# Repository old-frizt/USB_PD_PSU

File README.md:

# USB_PD_PSU
DIY USB Power Delivery Lab Bench Power Supply

WORK-IN-PROGRESS

This is a power supply with a linear ouput stage and a switching pre regulator.
In the future it will be controlled via a microcontroller doughter board.

The power to the supply is comes from USB Power-delivery at 20V.
The ouput can be set between 0-20V and 0-3A.

Additional information can be found on my website: https://arduonics.com/2020/electronics/diy-usb-power-delivery-lab-bench-power-supply/

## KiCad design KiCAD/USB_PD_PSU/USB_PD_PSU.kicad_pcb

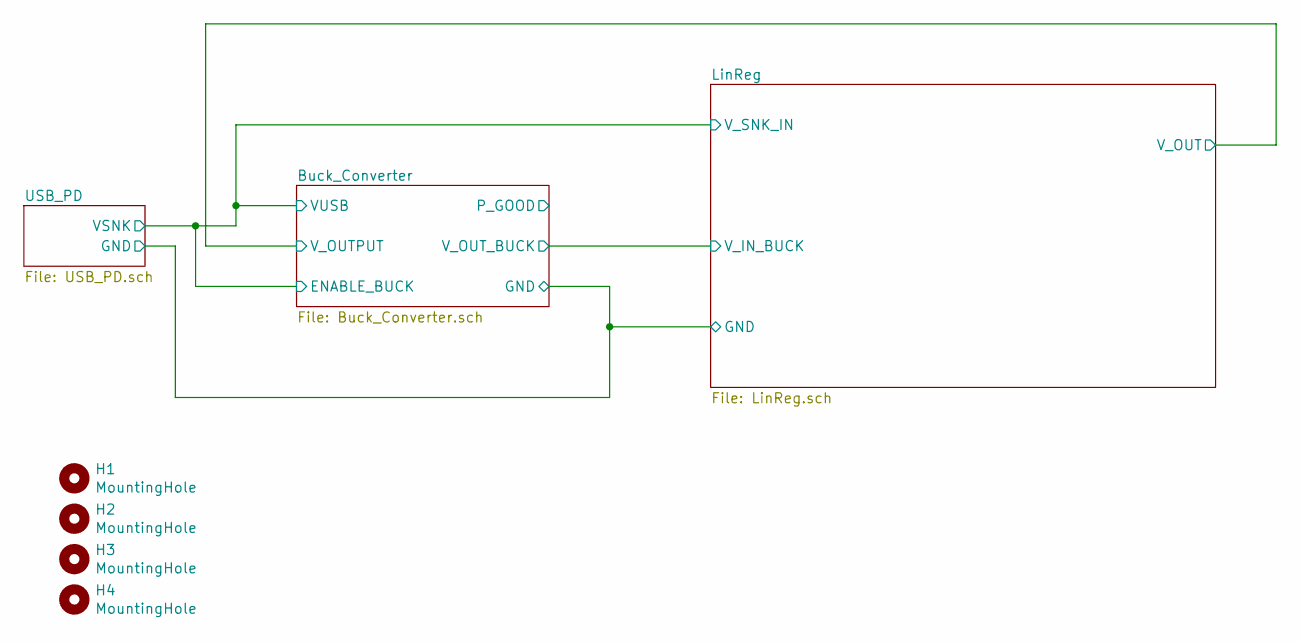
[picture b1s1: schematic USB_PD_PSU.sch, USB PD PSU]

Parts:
H1, H2, H3, H4: MountingHole; MountingHole_3.2mm_M3_Pad_Via

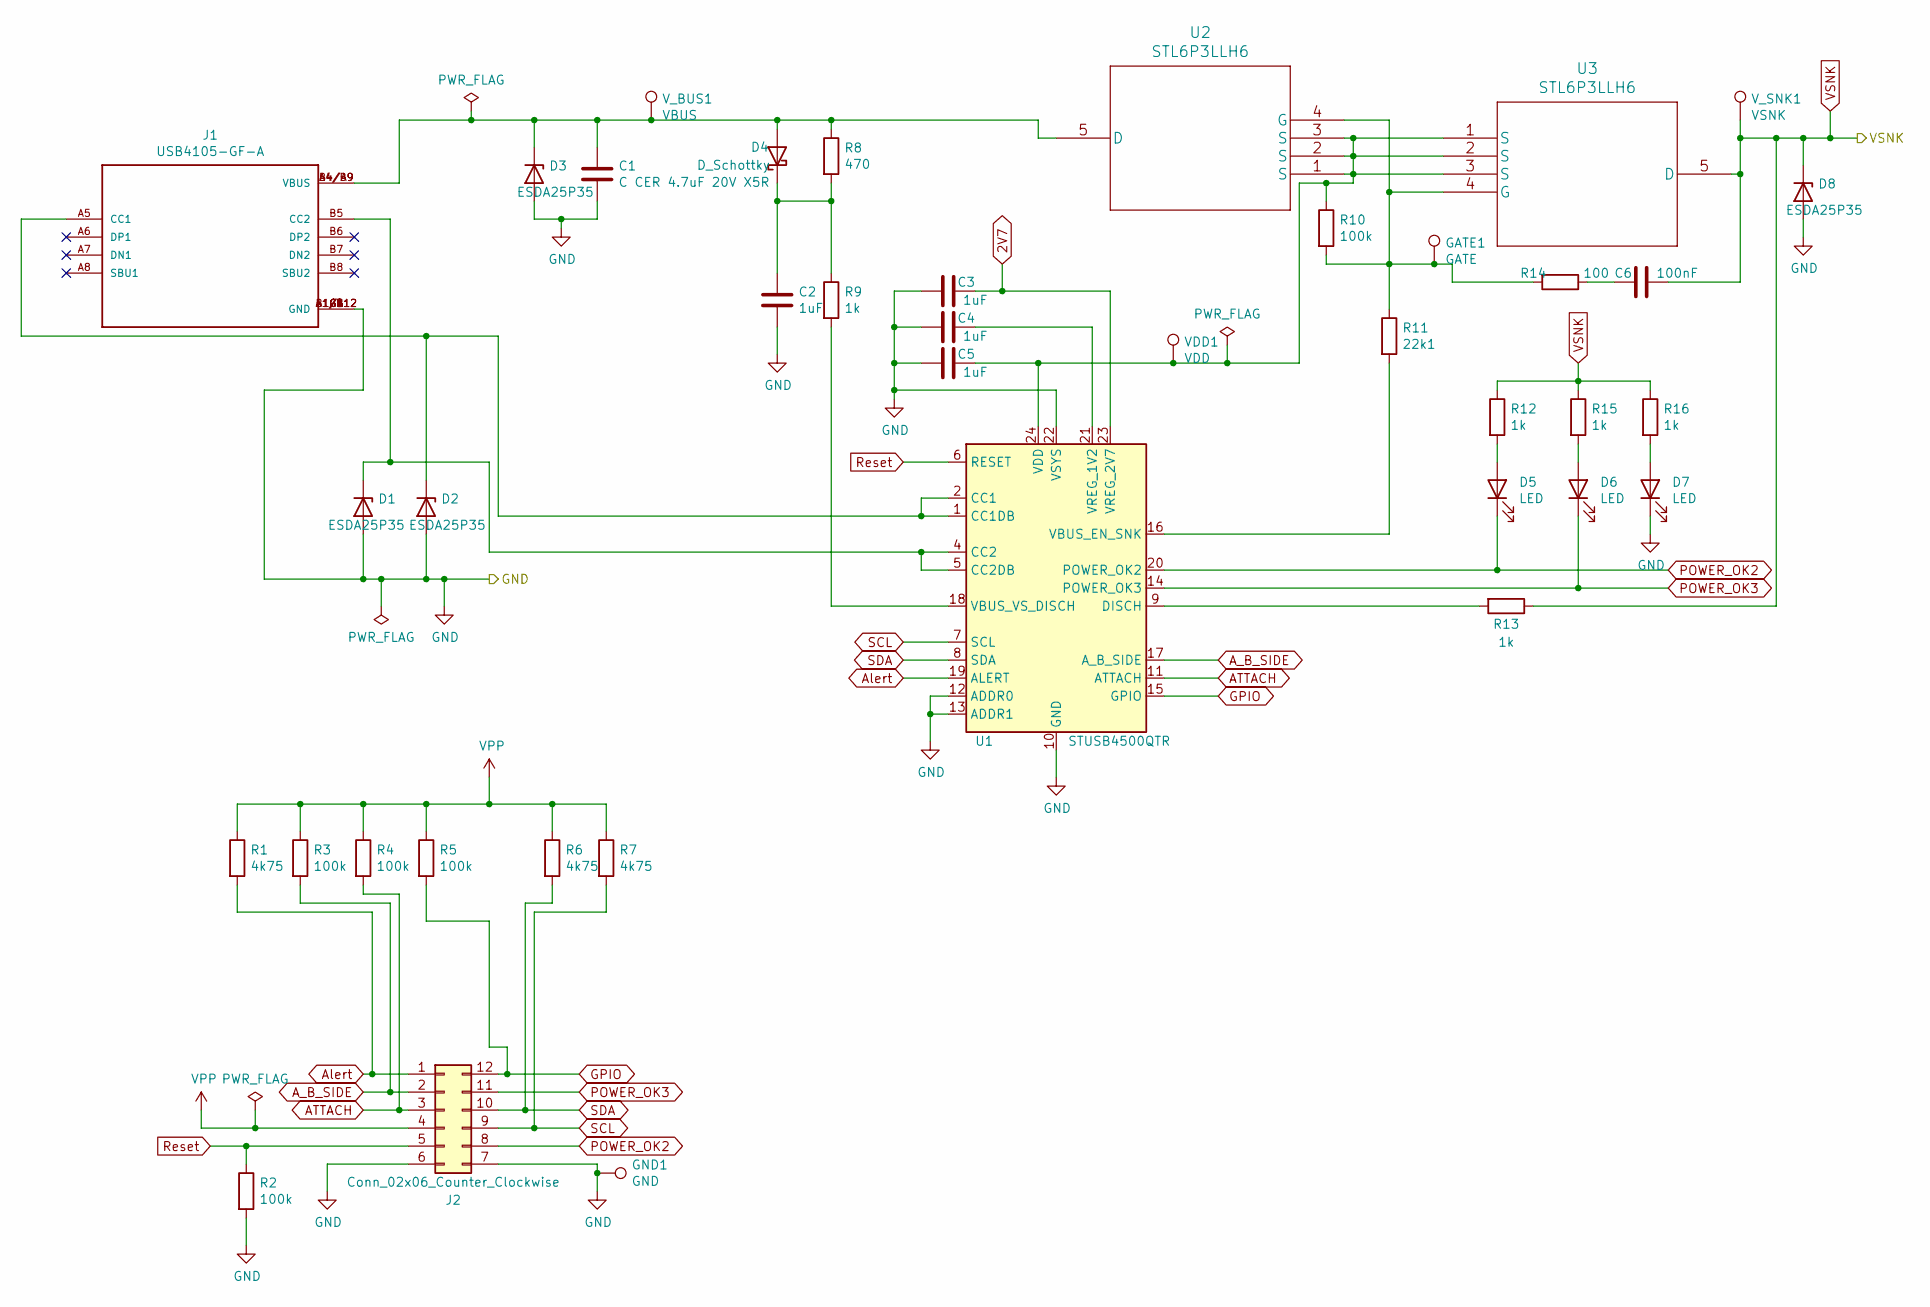
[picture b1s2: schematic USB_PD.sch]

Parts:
C1: C CER 4.7uF 20V X5R; C_0805_2012Metric_Pad1.15x1.40mm_HandSolder
C2, C3, C4, C5: 1uF; C_0805_2012Metric_Pad1.15x1.40mm_HandSolder
C6: 100nF; C_0805_2012Metric_Pad1.15x1.40mm_HandSolder
D1, D2, D3, D8: ESDA25P35; QFN_1610_2-UDFN_ESDA25P35; DigiKey 497-16913-1-ND‎
D4: D_Schottky; D_SOD-323_HandSoldering; DigiKey BAT54HT1GOSCT-ND
D5, D6, D7: LED; LED_0805_2012Metric_Pad1.15x1.40mm_HandSolder; DigiKey 732-4987-1-ND
GATE1: GATE; TestPoint_Pad_D2.0mm
GND1: GND; TestPoint_Pad_D2.0mm
J1: USB4105-GF-A; USB_C_Rec_USB4105-GF-A
J2: Conn_02x06_Counter_Clockwise; PinSocket_2x06_P2.54mm_Vertical
R1, R6, R7: 4k75; R_0805_2012Metric_Pad1.15x1.40mm_HandSolder
R2, R3, R4, R5, R10: 100k; R_0805_2012Metric_Pad1.15x1.40mm_HandSolder
R8: 470; R_0805_2012Metric_Pad1.15x1.40mm_HandSolder
R9, R12, R13, R15, R16: 1k; R_0805_2012Metric_Pad1.15x1.40mm_HandSolder
R11: 22k1; R_0805_2012Metric_Pad1.15x1.40mm_HandSolder
R14: 100; R_0805_2012Metric_Pad1.15x1.40mm_HandSolder
U1: STUSB4500QTR; QFN-24-1EP_4x4mm_P0.5mm_EP2.7x2.7mm; DigiKey 497-18060-1-ND
U2, U3: STL6P3LLH6; PowerFLAT_3.3x3.3; DigiKey 497-15315-1-ND
VDD1: VDD; TestPoint_Pad_D2.0mm
V_BUS1: VBUS; TestPoint_Pad_D2.0mm
V_SNK1: VSNK; TestPoint_Pad_D2.0mm

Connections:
2V7: C3.1, U1.23 (VREG_2V7)
ATTACH: J2.3, R4.2, U1.11 (ATTACH)
A_B_SIDE: J2.2, R3.2, U1.17 (A_B_SIDE)
Alert: J2.1, R1.2, U1.19 (ALERT)
GND: C1.2, C2.2, C3.2, C4.2, C5.2, D1.2 (A), D2.2 (A), D3.2 (A), D7.1 (K), D8.2 (A), GND1.1, J1.A1/B12 (GND), J1.B1/A12 (GND), J1.G1 (GND), J1.G2 (GND), J1.G3 (GND), J1.G4 (GND), J2.6, J2.7, R2.2, U1.10 (GND), U1.12 (ADDR0), U1.13 (ADDR1), U1.22 (VSYS), U1.25 (GND); also elsewhere on the board
GPIO: J2.12, R5.2, U1.15 (GPIO)
unnamed: C1.1, D3.1 (K), D4.2 (A), J1.A4/B9 (VBUS), J1.B4/A9 (VBUS), R8.1, U2.5 (D), V_BUS1.1
unnamed: C2.1, D4.1 (K), R8.2, R9.1
unnamed: C4.1, U1.21 (VREG_1V2)
unnamed: C5.1, R10.1, U1.24 (VDD), U2.1 (S), U2.2 (S), U2.3 (S), U3.1 (S), U3.2 (S), U3.3 (S), VDD1.1
unnamed: C6.1, R14.1
unnamed: D1.1 (K), J1.B5 (CC2), U1.4 (CC2), U1.5 (CC2DB)
unnamed: D2.1 (K), J1.A5 (CC1), U1.1 (CC1DB), U1.2 (CC1)
unnamed: D5.2 (A), R12.2
unnamed: D6.2 (A), R15.2
unnamed: D7.2 (A), R16.2
unnamed: GATE1.1, R10.2, R11.1, R14.2, U2.4 (G), U3.4 (G)
unnamed: R9.2, U1.18 (VBUS_VS_DISCH)
unnamed: R11.2, U1.16 (VBUS_EN_SNK)
unnamed: R13.2, U1.9 (DISCH)
POWER_OK2: D5.1 (K), J2.8, U1.20 (POWER_OK2)
POWER_OK3: D6.1 (K), J2.11, U1.14 (POWER_OK3)
Reset: J2.5, R2.1, U1.6 (RESET)
SCL: J2.9, R7.2, U1.7 (SCL)
SDA: J2.10, R6.2, U1.8 (SDA)
VPP: J2.4, R1.1, R3.1, R4.1, R5.1, R6.1, R7.1
VSNK: C6.2, D8.1 (K), R12.1, R13.1, R15.1, R16.1, U3.5 (D), V_SNK1.1; also elsewhere on the board

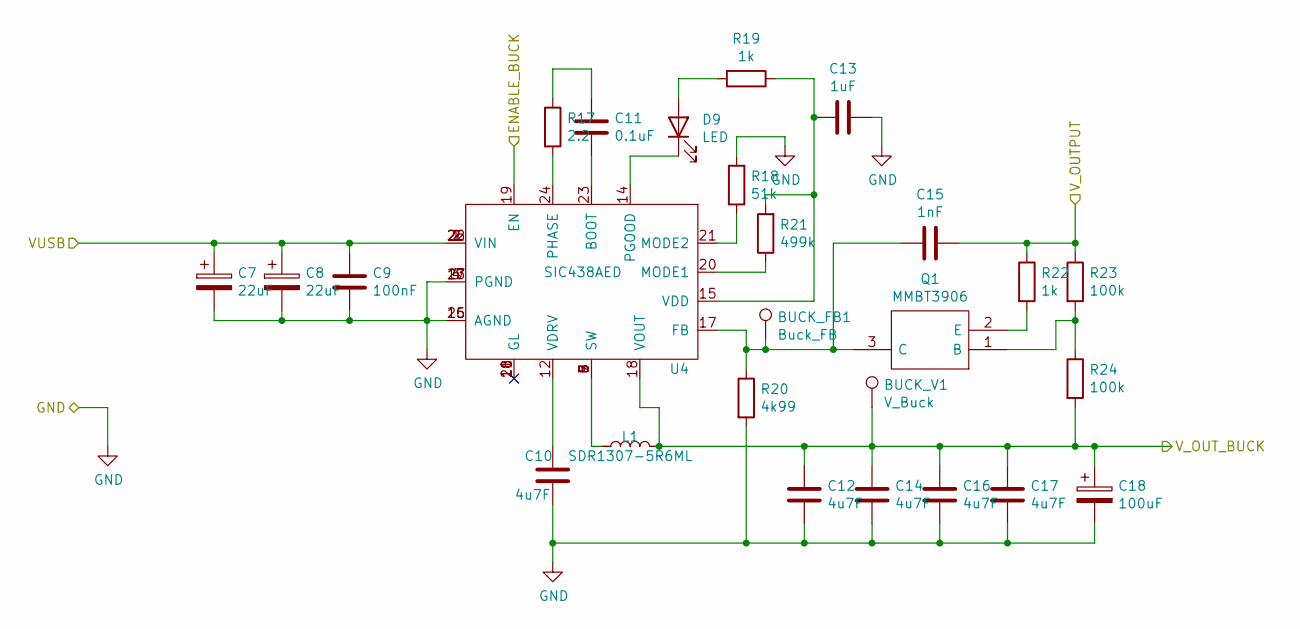
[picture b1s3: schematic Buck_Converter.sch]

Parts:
BUCK_FB1: Buck_FB; TestPoint_Pad_D2.0mm
BUCK_V1: V_Buck; TestPoint_Pad_D2.0mm
C7, C8: 22uF; CP_Elec_6.3x5.9; DigiKey 732-8453-1-ND
C9: 100nF; C_0805_2012Metric_Pad1.15x1.40mm_HandSolder
C10, C12, C14, C16, C17: 4u7F; C_0805_2012Metric_Pad1.15x1.40mm_HandSolder
C11: 0.1uF; C_0805_2012Metric_Pad1.15x1.40mm_HandSolder
C13: 1uF; C_0805_2012Metric_Pad1.15x1.40mm_HandSolder
C15: 1nF; C_0805_2012Metric_Pad1.15x1.40mm_HandSolder
C18: 100uF; CP_Elec_6.3x5.9; DigiKey 732-8511-1-ND
D9: LED; LED_0805_2012Metric_Pad1.15x1.40mm_HandSolder; DigiKey 732-4987-1-ND
L1: SDR1307-5R6ML; Inductor_SDR1307; DigiKey SDR1307-5R6MLCT-ND
Q1: MMBT3906; SOT-23; Mouser Part Number 512-MMBT3906
R17: 2.2; R_0805_2012Metric_Pad1.15x1.40mm_HandSolder; DigiKey RL12S2.20FCT-ND
R18: 51k; R_0805_2012Metric_Pad1.15x1.40mm_HandSolder
R19, R22: 1k; R_0805_2012Metric_Pad1.15x1.40mm_HandSolder
R20: 4k99; R_0805_2012Metric_Pad1.15x1.40mm_HandSolder
R21: 499k; R_0805_2012Metric_Pad1.15x1.40mm_HandSolder
R23, R24: 100k; R_0805_2012Metric_Pad1.15x1.40mm_HandSolder
U4: SIC438AED; MLP44-24L PowerPAK; DigiKey SIC438AED-T1-GE3CT-ND

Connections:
/LinReg/V_IN_BUCK: BUCK_V1.1, C12.1, C14.1, C16.1, C17.1, C18.1, L1.2, R24.2, U4.18 (VOUT); also elsewhere on the board
GND: C7.2, C8.2, C9.2, C10.2, C12.2, C13.1, C14.2, C16.2, C17.2, C18.2, R18.2, R20.2, U4.3 (PGND), U4.4 (PGND), U4.13 (PGND), U4.16 (AGND), U4.25 (AGND), U4.27 (PGND); also elsewhere on the board
unnamed: BUCK_FB1.1, C15.2, Q1.3 (C), R20.1, U4.17 (FB)
unnamed: C10.1, U4.12 (VDRV)
unnamed: C11.1, R17.1
unnamed: C11.2, U4.23 (BOOT)
unnamed: C13.2, R19.1, R21.2, U4.15 (VDD)
unnamed: D9.1 (K), U4.14 (PGOOD)
unnamed: D9.2 (A), R19.2
unnamed: L1.1, U4.5 (SW), U4.6 (SW), U4.7 (SW), U4.8 (SW), U4.9 (SW)
unnamed: Q1.1 (B), R23.2, R24.1
unnamed: Q1.2 (E), R22.2
unnamed: R17.2, U4.24 (PHASE)
unnamed: R18.1, U4.21 (MODE2)
unnamed: R21.1, U4.20 (MODE1)
unnamed: U4.10 (GL), U4.11 (GL), U4.28 (GL)
VSNK: C7.1, C8.1, C9.1, U4.1 (VIN), U4.2 (VIN), U4.19 (EN), U4.22 (VIN), U4.26 (VIN); also elsewhere on the board
V_OUTPUT: C15.1, R22.1, R23.1; also elsewhere on the board

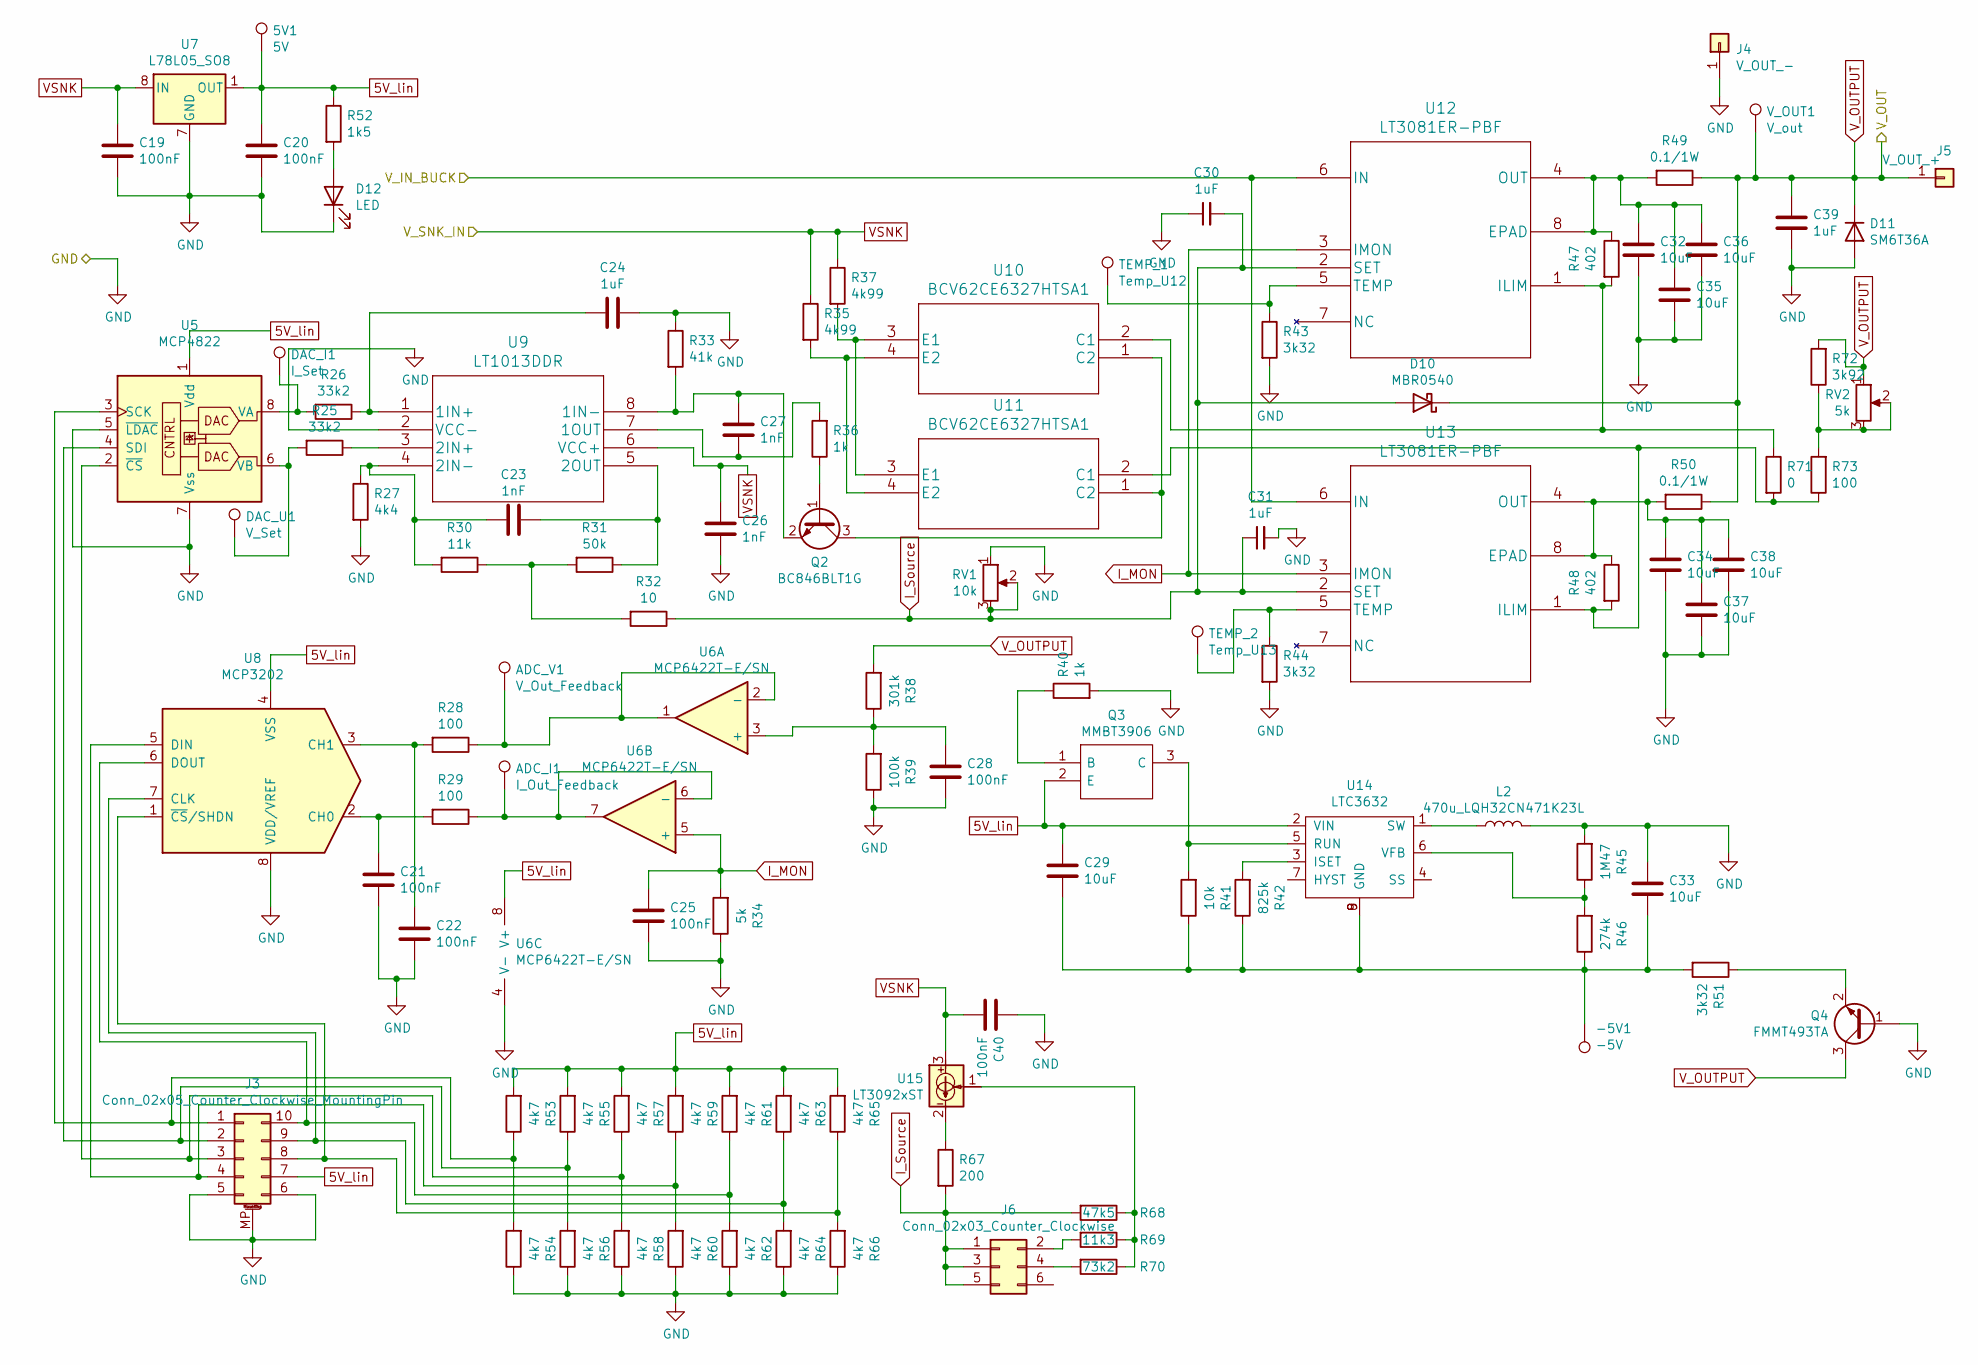
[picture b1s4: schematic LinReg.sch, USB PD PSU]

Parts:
5V1: 5V; TestPoint_Pad_D2.0mm
-5V1: -5V; TestPoint_Pad_D2.0mm
ADC_I1: I_Out_Feedback; TestPoint_Pad_D2.0mm
ADC_V1: V_Out_Feedback; TestPoint_Pad_D2.0mm
C19, C20, C21, C22, C25, C28, C40: 100nF; C_0805_2012Metric_Pad1.15x1.40mm_HandSolder
C23, C26, C27: 1nF; C_0805_2012Metric_Pad1.15x1.40mm_HandSolder
C24, C30, C31, C39: 1uF; C_0805_2012Metric_Pad1.15x1.40mm_HandSolder
C29, C32, C33, C34, C35, C36, C37, C38: 10uF; C_0805_2012Metric_Pad1.15x1.40mm_HandSolder
D10: MBR0540; D_SOD-123; DigiKey MBR0540T3GOSCT-ND
D11: SM6T36A; D_SMB_Handsoldering; DigiKey ‎497-6495-1-ND‎
D12: LED; LED_0805_2012Metric_Pad1.15x1.40mm_HandSolder
DAC_I1: I_Set; TestPoint_Pad_D2.0mm
DAC_U1: V_Set; TestPoint_Pad_D2.0mm
J3: Conn_02x05_Counter_Clockwise_MountingPin; PinSocket_2x05_P2.54mm_Vertical
J4: V_OUT_-; Banana_575-4
J5: V_OUT_+; Banana_575-4
J6: Conn_02x03_Counter_Clockwise; PinSocket_2x03_P2.54mm_Vertical
L2: 470u_LQH32CN471K23L; LQH32CN471K23L; DigiKey 490-2499-1-ND
Q2: BC846BLT1G; SOT-23; DigiKey BC846BLT1GOSCT-ND
Q3: MMBT3906; SOT-23; Mouser Part Number 512-MMBT3906
Q4: FMMT493TA; SOT-23; DigiKey FMMT493CT-ND
R25, R26: 33k2; R_0805_2012Metric_Pad1.15x1.40mm_HandSolder
R27: 4k4; R_0805_2012Metric_Pad1.15x1.40mm_HandSolder
R28, R29, R73: 100; R_0805_2012Metric_Pad1.15x1.40mm_HandSolder
R30: 11k; R_0805_2012Metric_Pad1.15x1.40mm_HandSolder
R31: 50k; R_0805_2012Metric_Pad1.15x1.40mm_HandSolder
R32: 10; R_0805_2012Metric_Pad1.15x1.40mm_HandSolder
R33: 41k; R_0805_2012Metric_Pad1.15x1.40mm_HandSolder
R34: 5k; R_0805_2012Metric_Pad1.15x1.40mm_HandSolder
R35, R37: 4k99; R_0805_2012Metric_Pad1.15x1.40mm_HandSolder
R36, R40: 1k; R_0805_2012Metric_Pad1.15x1.40mm_HandSolder
R38: 301k; R_0805_2012Metric_Pad1.15x1.40mm_HandSolder
R39: 100k; R_0805_2012Metric_Pad1.15x1.40mm_HandSolder
R41: 10k; R_0805_2012Metric_Pad1.15x1.40mm_HandSolder
R42: 825k; R_0805_2012Metric_Pad1.15x1.40mm_HandSolder
R43, R44, R51: 3k32; R_0805_2012Metric_Pad1.15x1.40mm_HandSolder
R45: 1M47; R_0805_2012Metric_Pad1.15x1.40mm_HandSolder
R46: 274k; R_0805_2012Metric_Pad1.15x1.40mm_HandSolder
R47, R48: 402; R_0805_2012Metric_Pad1.15x1.40mm_HandSolder
R49, R50: 0.1/1W; CFG0612; DigiKey LTC3632EMS8E#PBF-ND‎
R52: 1k5; R_0805_2012Metric_Pad1.15x1.40mm_HandSolder
R53, R54, R55, R56, R57, R58, R59, R60, R61, R62, R63, R64, R65, R66: 4k7; R_0805_2012Metric_Pad1.15x1.40mm_HandSolder
R67: 200; R_0805_2012Metric_Pad1.15x1.40mm_HandSolder
R68: 47k5; R_0805_2012Metric_Pad1.15x1.40mm_HandSolder
R69: 11k3; R_0805_2012Metric_Pad1.15x1.40mm_HandSolder
R70: 73k2; R_0805_2012Metric_Pad1.15x1.40mm_HandSolder
R71: 0; R_0805_2012Metric_Pad1.15x1.40mm_HandSolder
R72: 3k92; R_0805_2012Metric_Pad1.15x1.40mm_HandSolder
RV1: 10k; 84W_Trimmer; DigiKey 987-1806-1-ND‎
RV2: 5k; 84W_Trimmer; DigiKey ‎987-1810-1-ND‎
TEMP_1: Temp_U12; TestPoint_Pad_D2.0mm
TEMP_2: Temp_U13; TestPoint_Pad_D2.0mm
U5: MCP4822; SOIC-8_3.9x4.9mm_P1.27mm; DigiKey MCP4822-E/SN-ND‎
U6: MCP6422T-E/SN; SOIC-8_3.9x4.9mm_P1.27mm; DigiKey MCP6422T-E/SNCT-ND
U7: L78L05_SO8; SOIC-8_3.9x4.9mm_P1.27mm; DigiKey ‎497-7267-1-ND‎
U8: MCP3202; MSOP-8_3x3mm_P0.65mm; DigiKey MCP3202T-CI/MSCT-ND
U9: LT1013DDR; SOIC-8_3.9x4.9mm_P1.27mm; DigiKey 296-14615-1-ND‎
U10, U11: BCV62CE6327HTSA1; SOT-143; DigiKey ‎BCV62CE6327HTSA1CT-ND‎
U12, U13: LT3081ER-PBF; LT3081ER_7-DDPAK; DigiKey ‎LT3081ER#PBF-ND‎
U14: LTC3632; MSOP_MS8E; DigiKey LTC3632EMS8E#PBF-ND‎
U15: LT3092xST; SOT-223-3_TabPin2
V_OUT1: V_out; TestPoint_Pad_D2.0mm

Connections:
5V_lin: 5V1.1, C20.1, C29.1, J3.7, Q3.2 (E), R52.1, R53.2, R55.2, R57.2, R59.2, R61.2, R63.2, R65.2, U5.1 (Vdd), U6.8 (V+), U7.1 (OUT), U8.4 (VSS), U14.2 (VIN)
/LinReg/V_IN_BUCK: U12.6 (IN), U13.6 (IN); also elsewhere on the board
GND: C19.2, C20.2, C21.2, C22.2, C24.1, C25.2, C26.2, C28.2, C30.1, C31.2, C32.2, C33.1, C34.2, C35.2, C36.2, C37.2, C38.2, C39.2, C40.1, D11.2 (A), D12.1 (K), J3.5, J3.6, J3.MP (MountPin), J4.1, L2.2, Q4.1 (B), R27.2, R33.1, R34.1, R39.1, R40.2, R43.2, R44.2, R45.2, R54.1, R56.1, R58.1, R60.1, R62.1, R64.1, R66.1, RV1.1, U5.5 (~LDAC), U5.7 (Vss), U6.4 (V-), U7.2 (GND), U7.3 (GND), U7.6 (GND), U7.7 (GND), U8.8 (VDD/VREF), U9.2 (VCC-); also elsewhere on the board
I_MON: C25.1, R34.2, U6.5 (+), U12.3 (IMON), U13.3 (IMON)
I_Source: C30.2, C31.1, D10.2 (A), J6.1, J6.3, J6.5, R32.1, R67.2, R68.2, RV1.2, RV1.3, U12.2 (SET), U13.2 (SET)
unnamed: -5V1.1, C29.2, C33.2, R41.1, R42.1, R46.1, R51.2, U14.8 (GND), U14.9 (GND)
unnamed: ADC_I1.1, R29.1, U6.6 (-), U6.7
unnamed: ADC_V1.1, R28.1, U6.1, U6.2 (-)
unnamed: C21.1, R29.2, U8.2 (CH0)
unnamed: C22.1, R28.2, U8.3 (CH1)
unnamed: C23.1, R27.1, R30.2, U9.4 (2IN-)
unnamed: C23.2, R31.1, U9.5 (2OUT)
unnamed: C24.2, R26.1, U9.1 (1IN+)
unnamed: C27.1, Q2.2 (E), R33.2, U9.8 (1IN-)
unnamed: C27.2, R36.2, U9.7 (1OUT)
unnamed: C28.1, R38.1, R39.2, U6.3 (+)
unnamed: C32.1, C35.1, C36.1, R47.1, R49.2, U12.4 (OUT), U12.8 (EPAD)
unnamed: C34.1, C37.1, C38.1, R48.1, R50.2, U13.4 (OUT), U13.8 (EPAD)
unnamed: D12.2 (A), R52.2
unnamed: DAC_I1.1, R26.2, U5.8 (VA)
unnamed: DAC_U1.1, R25.2, U5.6 (VB)
unnamed: J3.1, R53.1, R54.2, U5.3 (SCK)
unnamed: J3.2, R55.1, R56.2, U5.4 (SDI)
unnamed: J3.3, R57.1, R58.2, U5.2 (~CS)
unnamed: J3.4, R59.1, R60.2, U8.5 (DIN)
unnamed: J3.8, R65.1, R66.2, U8.1 (~CS~/SHDN)
unnamed: J3.9, R63.1, R64.2, U8.7 (CLK)
unnamed: J3.10, R61.1, R62.2, U8.6 (DOUT)
unnamed: J6.2, R69.2
unnamed: J6.4, R70.2
unnamed: L2.1, U14.1 (SW)
unnamed: Q2.1 (B), R36.1
unnamed: Q2.3 (C), U10.1 (C2), U11.1 (C2)
unnamed: Q3.1 (B), R40.1
unnamed: Q3.3 (C), R41.2, U14.5 (RUN)
unnamed: Q4.2 (E), R51.1
unnamed: R25.1, U9.3 (2IN+)
unnamed: R30.1, R31.2, R32.2
unnamed: R35.2, U10.4 (E2), U11.4 (E2)
unnamed: R37.2, U10.3 (E1), U11.3 (E1)
unnamed: R42.2, U14.3 (ISET)
unnamed: R43.1, TEMP_1.1, U12.5 (TEMP)
unnamed: R44.1, TEMP_2.1, U13.5 (TEMP)
unnamed: R45.1, R46.2, U14.6 (VFB)
unnamed: R47.2, R71.1, U10.2 (C1), U12.1 (ILIM)
unnamed: R48.2, R71.2, R73.1, U11.2 (C1), U13.1 (ILIM)
unnamed: R67.1, U15.2
unnamed: R68.1, R69.1, R70.1, U15.1
unnamed: R72.1, R73.2, RV2.2, RV2.3
VSNK: C19.1, C26.1, C40.2, R35.1, R37.1, U7.8 (IN), U9.6 (VCC+), U15.3; also elsewhere on the board
V_OUTPUT: C39.1, D10.1 (K), D11.1 (K), J5.1, Q4.3 (C), R38.2, R49.1, R50.1, R72.2, RV2.1, V_OUT1.1; also elsewhere on the board

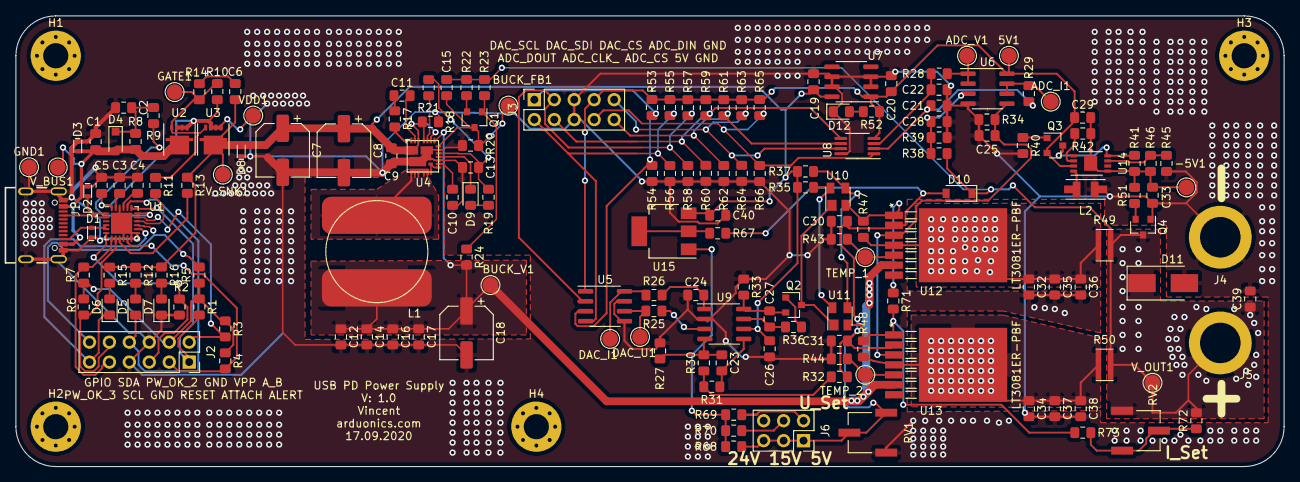
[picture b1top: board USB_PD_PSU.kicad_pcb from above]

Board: 2 copper layers, 161.5 x 57.4 mm, 174 parts (0 on the bottom side), 90 nets.

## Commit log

2020-09-18 inital commit
2020-09-19 updated schematic and pcb
2020-10-07 updated KiCad files, added Ibom
2020-10-08 removed outdated BOM

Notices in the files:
parts and their libraries:
Copyright 2016 Accelerated Designs. All rights reserved.
